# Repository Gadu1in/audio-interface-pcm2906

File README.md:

# audio-interface-pcm2906
An audio interface designed for low impedance earbuds and an external 3.5mm microphone input

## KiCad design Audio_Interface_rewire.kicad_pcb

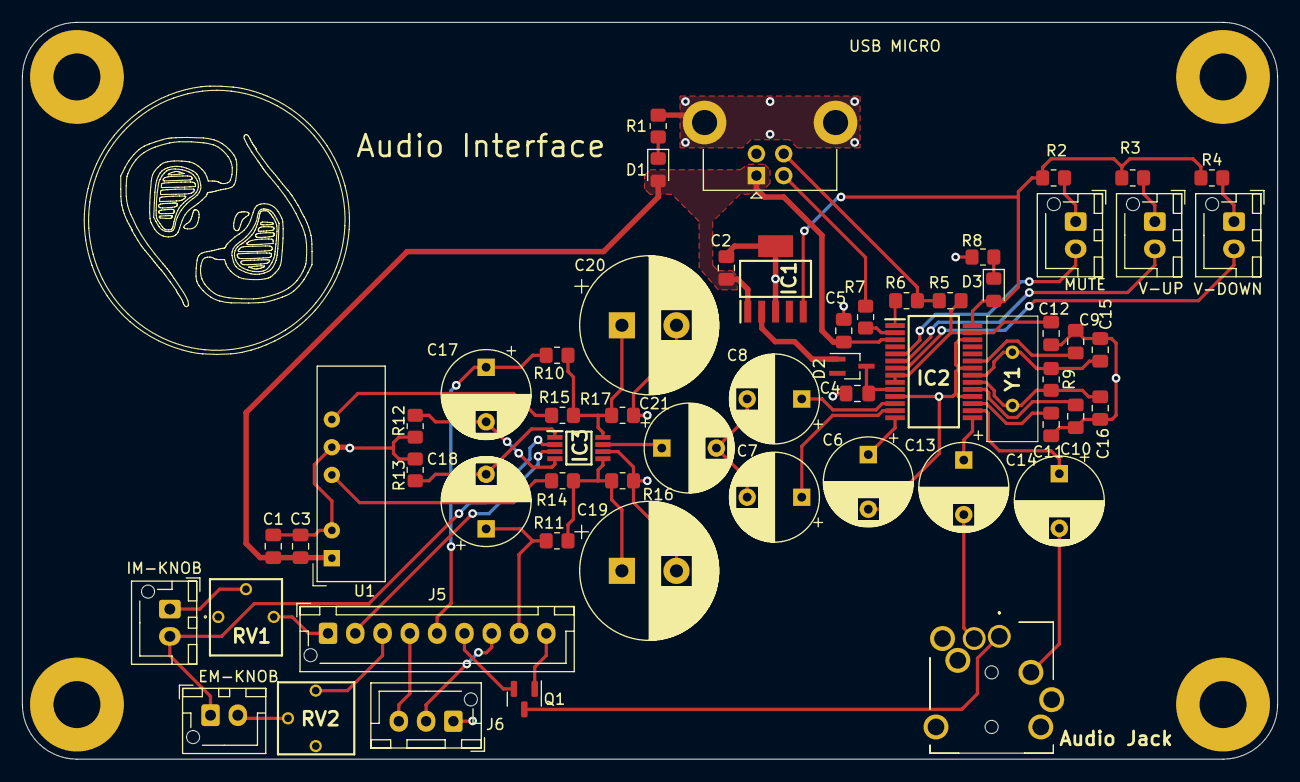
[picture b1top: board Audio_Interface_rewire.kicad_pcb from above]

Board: 2 copper layers, 115.0 x 67.5 mm, 62 parts (0 on the bottom side), 51 nets.

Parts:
Audio Jack: SJ-435107RS; SJ435107RS
C1, C3: 2200uF; C_0805_2012Metric_Pad1.18x1.45mm_HandSolder
C2: 100nF; C_0805_2012Metric_Pad1.18x1.45mm_HandSolder
C4: 10uF; C_0805_2012Metric_Pad1.18x1.45mm_HandSolder
C5, C9, C10, C11, C12: 1uF; C_0805_2012Metric_Pad1.18x1.45mm_HandSolder
C6, C13, C14: 10uF; CP_Radial_D8.0mm_P5.00mm
C7, C8: 4u7F; CP_Radial_D8.0mm_P5.00mm
C15, C16: 27pF; C_0805_2012Metric_Pad1.18x1.45mm_HandSolder
C17, C18, C21: 22uF; CP_Radial_D8.0mm_P5.00mm
C19, C20: 2200uF 16 V; CP_Radial_D12.5mm_P5.00mm
D1: PWR_ON; D_0805_2012Metric_Pad1.15x1.40mm_HandSolder
D2: BAT54_R1_00001; SOT-323_SC-70_Handsoldering
D3: CONTINUE; D_0805_2012Metric_Pad1.15x1.40mm_HandSolder
EM-KNOB: Vol. knob1 22k; JST_XH_B2B-XH-AM_1x02_P2.50mm_Vertical
H1, H2, H3, H4: M4; MountingHole_4.3mm_M4_Pad
IC1: REG103GA-3.3_2K5; SOT127P706X180-6N
IC2: PCM2906CDB; SOP65P780X200-28N
IC3: INA849DGKT; SOP65P490X110-8N
IM-KNOB: Vol. knob2 22k; JST_XH_B2B-XH-AM_1x02_P2.50mm_Vertical
J5: SW_PUSH_3PDT; JST_XH_B9B-XH-AM_1x09_P2.50mm_Vertical
J6: External mic. conn.; JST_XH_B3B-XH-AM_1x03_P2.50mm_Vertical
MUTE: HID0; JST_XH_B2B-XH-AM_1x02_P2.50mm_Vertical
Q1: J304; SOT-23
R1, R8: 1k; R_0805_2012Metric_Pad1.20x1.40mm_HandSolder
R2, R3, R4, R5: 1k5; R_0805_2012Metric_Pad1.20x1.40mm_HandSolder
R6, R7: 22; R_0805_2012Metric_Pad1.20x1.40mm_HandSolder
R9: 1M; R_0805_2012Metric_Pad1.20x1.40mm_HandSolder
R10, R11, R16, R17: 2k2; R_0805_2012Metric_Pad1.20x1.40mm_HandSolder
R12, R13: 3k9; R_0805_2012Metric_Pad1.20x1.40mm_HandSolder
R14, R15: 100; R_0805_2012Metric_Pad1.20x1.40mm_HandSolder
RV1, RV2: 5k; 3362P_1
U1: NMA0515SC; Converter_DCDC_Murata_NMAxxxxSC_THT
USB MICRO: USB_B_Micro; USB_B_Lumberg_2411_02_Horizontal
V-DOWN: HID2; JST_XH_B2B-XH-AM_1x02_P2.50mm_Vertical
V-UP: HID1; JST_XH_B2B-XH-AM_1x02_P2.50mm_Vertical
Y1: 12MHz; HC49US12000000ABJB

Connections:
+3.3V: D2.1 (A), IC1.2 (VOUT)
+15V: R15.1, U1.6 (VOUT+)
-15V: R14.1, U1.4 (VOUT-)
/+vs: C20.1, IC3.8 (+VS), R10.1, R15.2, R17.1
/-vs: C19.1, IC3.5 (-VS), R11.2, R14.2, R16.1
/Audio_signal: C7.2, C8.2, C21.2
/EXT_MIC_D: J5.7, J6.2
/EXT_MIC_S: J5.4, J6.3
/HID0: IC2.5 (HID0), MUTE.2
/HID1: IC2.6 (HID1), V-UP.2
/HID2: IC2.7 (HID2), V-DOWN.2
/Headphones mic: Audio Jack.1 (SLEEVE), Q1.3 (G)
/INT_MIC_D: J5.9, Q1.1 (S)
/INT_MIC_S: J5.6, Q1.2 (D)
/RG_1: EM-KNOB.1, IC3.2 (RG_1), IM-KNOB.2
/RG_2: IC3.3 (RG_2), J5.2
/USB_D+: R5.1, R6.2, USB MICRO.3 (D+)
/USB_D-: R7.2, USB MICRO.2 (D-)
/VDDI: C12.1, IC2.8 (SEL0), IC2.9 (SEL1), IC2.27 (VDDI), R5.2
/V_IN_D: C18.1, J5.8, R11.1
/V_IN_S: C17.1, J5.5, R10.2
/V_OUT_L: Audio Jack.2 (TIP), C14.2
/V_OUT_R: Audio Jack.3 (RING_1), C13.2
/XTI_Crystal: C15.1, IC2.21 (XTI), R9.1, Y1.2
/XTO_Crystal: C16.2, IC2.20 (XTO), R9.2, Y1.1
/ext_mic: J5.3, RV2.3
/hp_mic: J5.1, RV1.3
/~SSPND: D3.2 (A), IC1.5 (ENABLE), IC2.28 (~SSPND), R2.1, R3.1, R4.1
GND: Audio Jack.4 (RING_2), C1.2, C2.1, C3.2, C4.2, C5.1, C6.2, C9.2, C10.2, C11.2, C12.2, C15.2, C16.1, C19.2, C20.2, IC1.3 (GND_1), IC1.6 (GND_2), IC2.4 (DGNDU), IC2.11 (AGNDC), IC2.18 (AGNDP), IC2.22 (AGNDX), IC2.26 (DGND), IC3.6 (REF), J6.1, R1.1, R8.2, R12.2, R13.2, R16.2, R17.2, U1.2 (VIN-), U1.5 (0V), USB MICRO.5 (GND)
unnamed: C4.1, D2.3 (K), IC2.10 (VCCCI)
unnamed: C6.1, IC2.14 (VCOM)
unnamed: C7.1, IC2.13 (VINR)
unnamed: C8.1, IC2.12 (VINL)
unnamed: C9.1, IC2.23 (VCCXI)
unnamed: C10.1, IC2.19 (VCCP2I)
unnamed: C11.1, IC2.17 (VCCP1I)
unnamed: C13.1, IC2.15 (VOUTR)
unnamed: C14.1, IC2.16 (VOUTL)
unnamed: C17.2, IC3.4 (+IN), R12.1
unnamed: C18.2, IC3.1 (-IN), R13.1
unnamed: C21.1, IC3.7 (OUT)
unnamed: D1.1 (K), R1.2
unnamed: D3.1 (K), R8.1
unnamed: IC2.1 (D+), R6.1
unnamed: IC2.2 (D-), R7.1
unnamed: EM-KNOB.2, RV2.2
unnamed: IM-KNOB.1, RV1.2
unnamed: MUTE.1, R2.2
unnamed: R3.2, V-UP.1
unnamed: R4.2, V-DOWN.1
VBUS: C1.1, C2.2, C3.1, C5.2, D1.2 (A), IC1.1 (VIN), IC2.3 (VBUS), U1.1 (VIN+), USB MICRO.1 (VBUS)

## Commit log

2022-11-14 Added my project to git
2022-11-14 First draft of schematic completed
2022-11-15 Started assigning footprints for pcb, about 1/2 completed
2022-11-17 Fixed gain control and added resistor footprints
2022-11-18 Completed first draft of footprint assignment
2022-11-19 First draft of pcb layout completed
2022-11-27 Changed microphone input system
2022-11-27 added footprint for 3pdt switch and ext mic
2022-11-28 started wiring the pcb
2022-11-29 finished the pcb design
2022-12-02 new pcb
2022-12-02 Reviewed Gnorins work
2022-12-03 Finished pcb layout for version 2.0
2022-12-03 Revert "Finished pcb layout for version 2.0"
    This reverts commit 9c98f4441856926bdc06a9c73f1d06339f9013c3. Pushed to wrong branch
2022-12-06 Uploading verion 2.0
2022-12-09 Moved crystal closer to IC2
    Moved the crystal closer to the IC2 and rewired some capacitors and resistors.
2022-12-09 Changed some labels
2022-12-09 Adding some zip files to backups
    we dont want to destroy anything...
2022-12-09 Fixed the final design
    Added a logo and fixed some readabiliy and cosmetics for the PCB
2023-02-17 New version without consideration for microphone on earbuds
